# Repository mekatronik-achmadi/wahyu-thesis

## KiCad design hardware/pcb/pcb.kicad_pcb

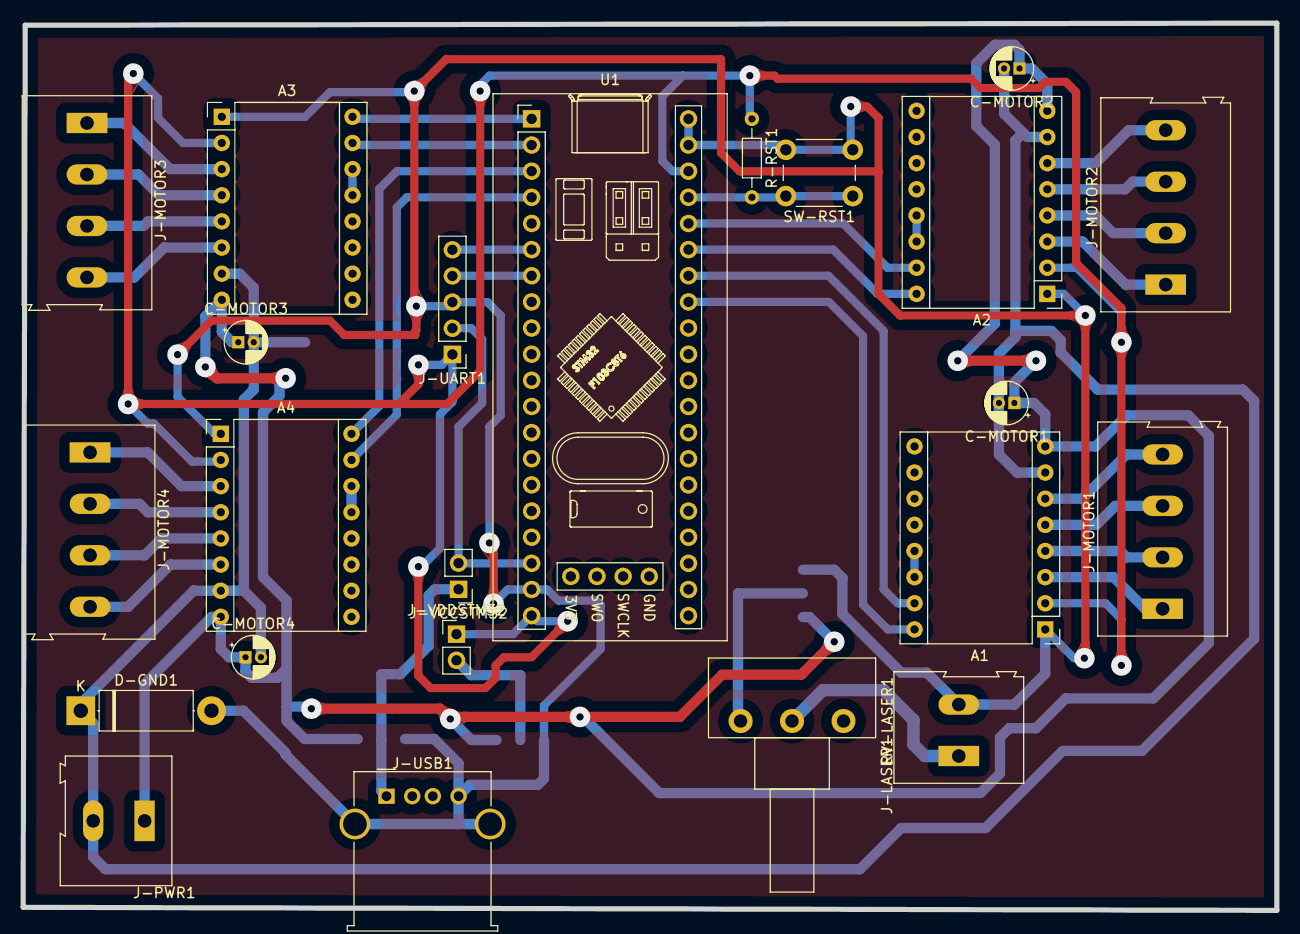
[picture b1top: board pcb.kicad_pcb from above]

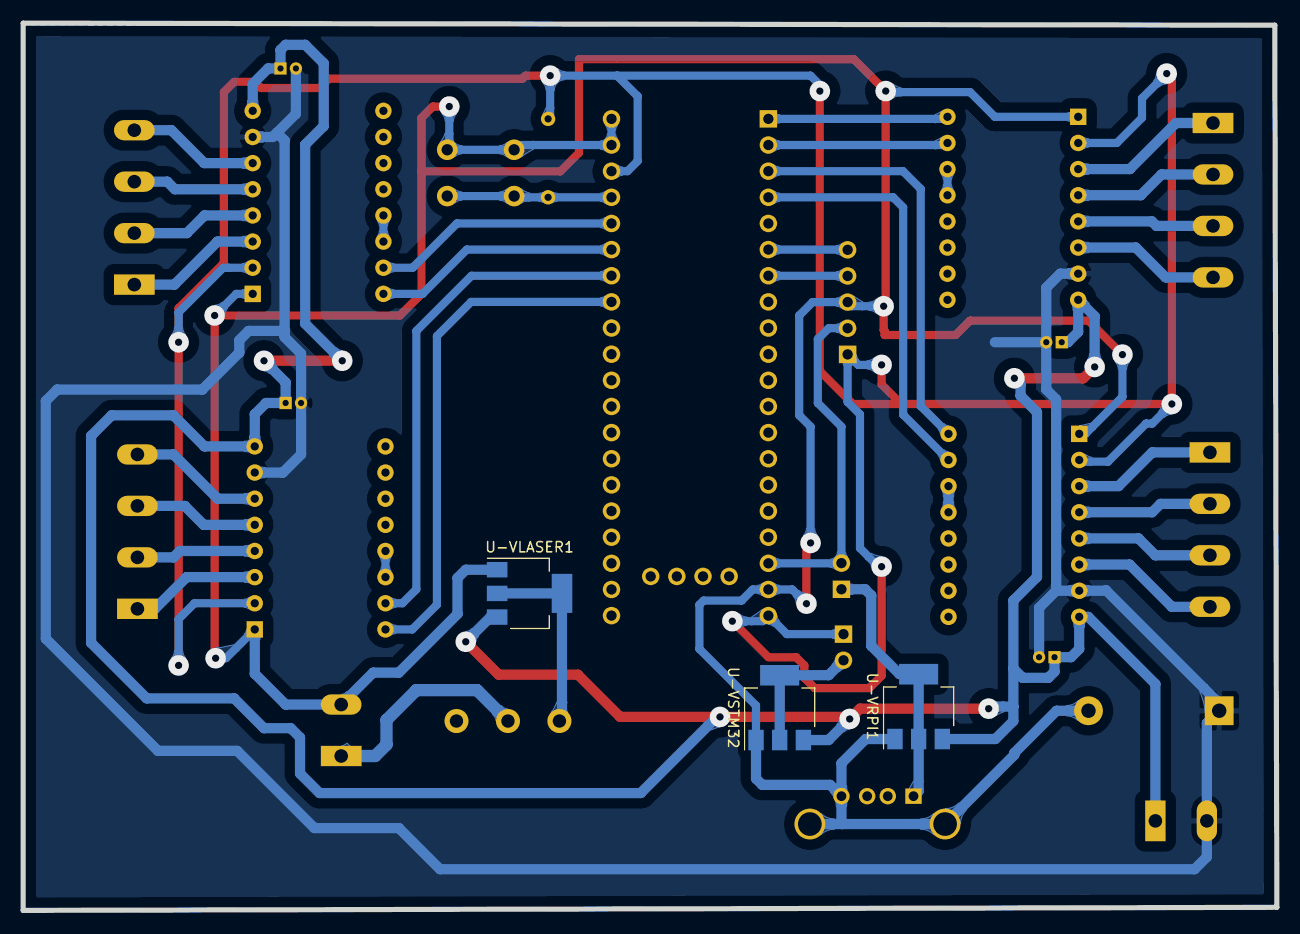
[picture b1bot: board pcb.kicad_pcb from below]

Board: 2 copper layers, 121.8 x 86.2 mm, 26 parts (3 on the bottom side), 40 nets.

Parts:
A1, A2, A3, A4: Pololu_Breakout_A4988; Pololu_Breakout-16_15.2x20.3mm
C-MOTOR1, C-MOTOR2, C-MOTOR3, C-MOTOR4: 100uF; CP_Radial_D4.0mm_P1.50mm
D-GND1: D; D_5W_P12.70mm_Horizontal
J-LASER1: Conn_01x02_Female; TerminalBlock_Altech_AK300-2_P5.00mm
J-MOTOR1, J-MOTOR2, J-MOTOR3, J-MOTOR4: Conn_01x04_Female; TerminalBlock_Altech_AK300-4_P5.00mm
J-PWR1: Conn_01x02_Female; TerminalBlock_Altech_AK300-2_P5.00mm
J-UART1: Conn_01x05_Female; PinHeader_1x05_P2.54mm_Vertical
J-USB1: USB_A; USB_A_Molex_67643_Horizontal
J-VCCSTM32: Conn_01x02_Female; PinHeader_1x02_P2.54mm_Vertical
J-VDDSTM32: Conn_01x02_Female; PinHeader_1x02_P2.54mm_Vertical
R-RST1: 10k; R_Axial_DIN0204_L3.6mm_D1.6mm_P7.62mm_Horizontal
RV-LASER1: R_POT; Potentiometer_Piher_T-16H_Single_Horizontal
SW-RST1: SW_Push; SW_PUSH_6mm
U1: YAAJ_BluePill_Part_Like_SWD_Breakout; YAAJ_BluePill_SWD_1
U-VLASER1: AMS1117-3.3; SOT-223-3_TabPin2
U-VRPI1: AMS1117-5.0; SOT-223-3_TabPin2
U-VSTM32: AMS1117-3.3; SOT-223-3_TabPin2

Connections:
+3V3: J-VDDSTM32.2, U-VSTM32.2
+5V: J-USB1.1, J-VCCSTM32.1, U-VRPI1.2
+12V: A1.8, A2.8, A3.8, A4.8, C-MOTOR1.1, C-MOTOR2.1, C-MOTOR3.1, C-MOTOR4.1, J-PWR1.1, U-VLASER1.3, U-VRPI1.3, U-VSTM32.3
/M1_DR: A1.16, U1.33
/M1_ST: A1.15, U1.34
/M2_DR: A2.16, U1.35
/M2_ST: A2.15, U1.36
/M3_DR: A3.16, U1.1
/M3_ST: A3.15, U1.2
/M4_DR: A4.16, U1.3
/M4_ST: A4.15, U1.4
/RST: R-RST1.2, SW-RST1.1, U1.37
/RX: J-UART1.4, U1.7
/TX: J-UART1.5, U1.6
GND: A1.1, A2.1, A3.1, A4.1, D-GND1.2, J-LASER1.2, J-UART1.3, J-USB1.4, J-USB1.5, SW-RST1.2, U1.19, U1.39, U1.40, U-VLASER1.1, U-VRPI1.1, U-VSTM32.1
GNDPWR: A1.7, A2.7, A3.7, A4.7, C-MOTOR1.2, C-MOTOR2.2, C-MOTOR3.2, C-MOTOR4.2, D-GND1.1, J-PWR1.2
unnamed: A1.3, J-MOTOR1.1
unnamed: A1.4, J-MOTOR1.2
unnamed: A1.5, J-MOTOR1.3
unnamed: A1.6, J-MOTOR1.4
unnamed: A1.13, A1.14
unnamed: A2.3, J-MOTOR2.1
unnamed: A2.4, J-MOTOR2.2
unnamed: A2.5, J-MOTOR2.3
unnamed: A2.6, J-MOTOR2.4
unnamed: A2.13, A2.14
unnamed: A3.3, J-MOTOR3.1
unnamed: A3.4, J-MOTOR3.2
unnamed: A3.5, J-MOTOR3.3
unnamed: A3.6, J-MOTOR3.4
unnamed: A3.13, A3.14
unnamed: A4.3, J-MOTOR4.1
unnamed: A4.4, J-MOTOR4.2
unnamed: A4.5, J-MOTOR4.3
unnamed: A4.6, J-MOTOR4.4
unnamed: A4.13, A4.14
unnamed: J-LASER1.1, RV-LASER1.2
unnamed: RV-LASER1.1, U-VLASER1.2
VCC: J-UART1.2, J-VCCSTM32.2, U1.18
VDD: A1.2, A2.2, A3.2, A4.2, J-UART1.1, J-VDDSTM32.1, R-RST1.1, U1.20, U1.38

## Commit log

2021-02-26 pcb awal
2021-02-28 progres
2021-03-06 progress
2021-03-15 qt creator files
2021-03-15 shell commands new
2021-03-15 motor testing
2021-03-15 progressing
2021-03-15 some improve path
2021-03-15 more motors functions
2021-03-15 firmware documentation
2021-03-21 motor status
2021-03-26 UART Serial
2021-03-30 archlinux arm
2021-03-30 archlinuxarm
2021-03-30 motor speed
2021-03-31 raspi wifi
